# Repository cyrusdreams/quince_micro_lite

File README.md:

# Introduction

The 10-cent-microcontroller, it was everywhere in the news. With a 32bit RISC-V core and useful peripherals, the CH32V003 from WCH is suited to many projects. But such a small microcontroller needs to be programmed via a dedicated adapter. In a forum at mikrocontroller.net, user F.P. analyzed the WCH LinkE debugging adapter and came to the conclusion that the binary code from WCH can be run on the USB enabled CH32V305 microcontroller. And because the CH32V305 can do so much more than its smaller sibling, the idea of this development board was born.

This description is valid for the 'lite' variant of said development board and its second production release version '1.0'.

# Features of the Quince micro lite

-   board dimensions of 21 mm \* 51 mm are the same as a *RaspberryPi Pico*, but it lacks the mounting holes, due to the use of an USB-C connector

-   the pinout of the board is designed to match the peripherals on the *ClockworkPi Pico Calc* mainboard

-   the boards has mounting pads for a microSD card slot and a connector for an OLED screen, if those are mounted, the board has the same features as a *Longan Nano*

-   the *LinkE* debug connector is found on the PCB edge, the "lite" version omits the switchable target supply voltages

-   on the bottom side of the PCB, a CAN bus transceiver can be mounted, this makes the Quince micro a small CAN bus node

-   a RGB LED can be controlled from the microcontroller, two of the LEDs share the port with the Rx/Tx lines of the debug interface

## Pinout of the Quince micro

The coloured signals match the ones on a *Raspberry Pi Pico*.

Remark: ports PB8 and PB9 are exchanged in the v0.9 revision of the *Quince micro lite*.

## Quince micro compared to the Longan nano

On the bottom side of the *Quince micro*, additional parts can be assembled to have a similar functionality as a *Longan nano* development board:

-   microSD slot, the port pins are also available on pins 21, 22, 24 and 25 of the *Quince micro*

-   eight-pin connector for OLED displays

## Quince micro as a CAN bus node

On the bottom side of the PCB, a CAN bus transceiver can be mounted (position U50) with its decoupling capacitor (C51, 100nF) and a four pole SMD pin header. With the available signals CAN-high, CAN-low, 5V-supply and Ground, the Quince micro can be supplied with power and act as a CAN bus node.

Recommended are CAN-SIC transceivers (Signal Improvement Capability), if the additional cost of approximately 0.15€ is bearable for the intended project. These newer transceivers enable higher data rates and/or longer wiring distances than older CAN-FD transceivers. For *Quince micro*, CAN transceivers with 'standby' input and separate IO voltage are suitable. Examples of compatible transceivers are TJA1462 , TCAN1462, TLE9371VSJ and others.

# Quince micro is a Debugger

## Features of the Quince micro as a WCH LinkE Debugger

On the short side of the PCB, opposite of the USB-S connector, there are solder pads suitable for two sets of five pin headers. The pinout is close to the *WCH LinkE R0 1v3*; the power supply pins are not switchable. Also not available is the "ModeSelect" button. Its functionality can be controlled via software, as stated in the "WCH-LinkUserManual" (version V2.4).

## Setup of the Quince micro as a LinkE Debugger

In the forum of mikrocontroller.net, user [Benutzer F.P. (fail)](https://www.mikrocontroller.net/user/show/fail) posted the following [Instructions](https://www.mikrocontroller.net/topic/578672#7974902) that are similar for the *Quince micro*:

1.  Install the software from WCH, commands for Linux:

    1.  git clone https://github.com/ch32-rs/wchisp

    2.  git clone https://github.com/ch32-rs/wlink

2.  Build the software (see respective documentation)

3.  Put the microcontroller into the USB programming mode

    1.  unpower the Quince micro

    2.  push and hold BOOT0 switch

    3.  connect USB to a PC

    4.  release BOOT0 switch

4.  Flash the firmware from MounRiverStudio (see [mikrocontroller.net)](https://www.mikrocontroller.net/attachment/672558/WCH-LinkE-APP-IAP.bin)

    1.  wchisp flash WCH-LinkE-APP-IAP.bin

5.  restart the Quince micro: unplug USB, reconnect USB

Now the Quince micro is ready to function as a WCH-LinkE adapter. After connecting it to another CH32 target (for example another Quince micro), the second microcontroller can be programmed with, for example:

1.  wlink flash blink.bin

The connection to a second Quince micro is done by connecting the pins SWDIO and SWCLK of both boards.

# Developing Software for the Quince micro

## MounRiver Studio

MounRiver Studio is the IDE preferred by WCH.

## Arduino

WCH has released their own Arduino core. With it, the CH32V305-Microcontroller of the Qince micro can be programmed with the Arduino IDE. The board itself is not available in the IDE, but the peripherals can be addressed as on the development board 'CH32V305RBT6'. The following pins (D\* and A\*) are available:

## PlatformIO

There is a GitHub repositry for [CH32V](https://github.com/Community-PIO-CH32V/platform-ch32v) in the PlatformIO IDE.

## cnlohr / ch32fun

Developer and YouTuber CNLohr (Charles) released his own development environment for CH32V with the name [ch32fun](https://github.com/cnlohr/ch32fun) on GitHub.

## Python

There is an [experimental port](https://github.com/r4d10n/micropython-wch-ch32v307/tree/master/ports/wch) of MicroPython for the CH32V307, this should also be useable for the CH32V305.

# Annex

## Revision History

### Revision v0.9

First production data.

### Revision v1.0

-   Changed the connection of PB8 and PB9 to match the RaspberryPi pinout, enabling an additional IC bus.

-   Connected 5V and 3.3V to the debug connector (non-switchable supply)

## Copyright

This text is licensed by CC-BY-SA-4.0. Product names and other trademarks are in the possession of their respective owners. This text makes no claim regarding those names but needs to use them for documentation and clarification purposes.

The Quince micro lite board itself is licensed via CERN-OHL-S-2.0, modifications and improvements are welcome.

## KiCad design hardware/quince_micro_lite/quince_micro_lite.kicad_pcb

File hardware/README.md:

# quince_micro_lite
A CH32V305 development board with Debugger option. Capable of interfacing with a PicoCalc mainboard.

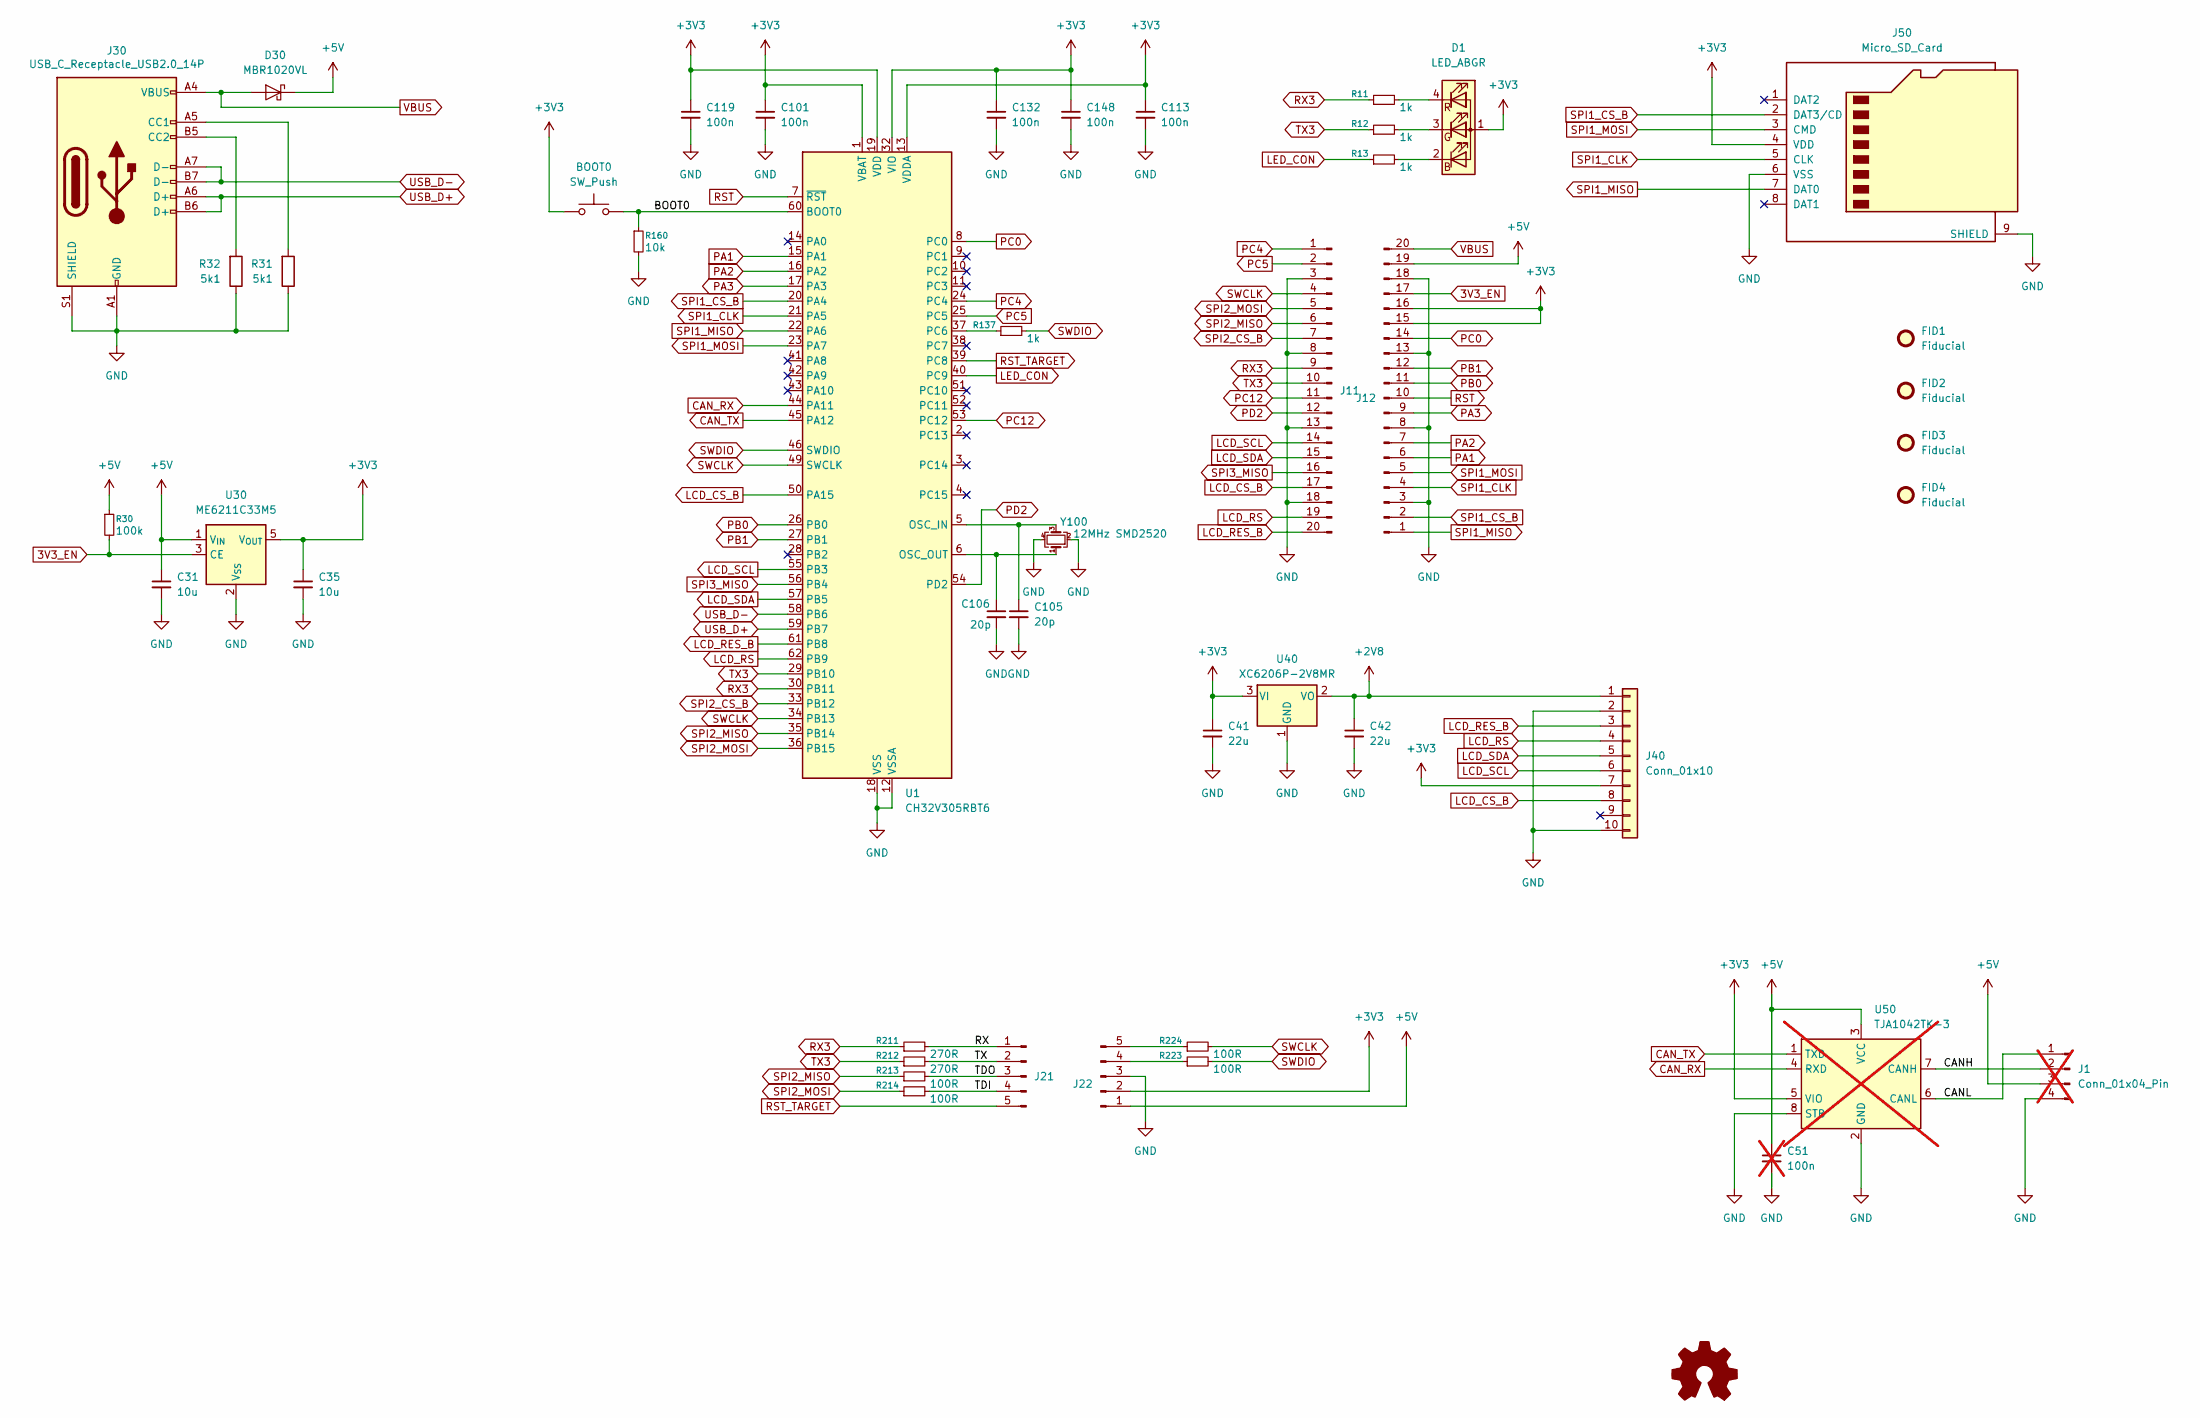
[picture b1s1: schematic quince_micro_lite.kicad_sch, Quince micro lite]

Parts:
BOOT0: SW_Push; SW_SPST_B3U-1000P
C31, C35: 10u; C_0603_1608Metric
C41, C42: 22u; C_0603_1608Metric
C51: 100n; C_0603_1608Metric_Pad1.08x0.95mm_HandSolder; not fitted
C101, C113, C119, C132, C148: 100n; C_0402_1005Metric
C105, C106: 20p; C_0402_1005Metric
D1: LED_ABGR; LED_Cree-PLCC4_2x2mm_CW
D30: MBR1020VL; D_SOD-123F
FID1, FID2, FID3, FID4: Fiducial; Fiducial_0.5mm_Mask1mm
J1: Conn_01x04_Pin; PinHeader_2x02_P2.54mm_Vertical_SMD; not fitted
J11, J12: Conn_01x20_Pin; PinHeader_1x20_P2.54mm_Vertical
J21, J22: Conn_01x05_Pin; Harwin_M20-89005xx_1x05_P2.54mm_Horizontal
J30: USB_C_Receptacle_USB2.0_14P; USB_C_Receptacle_G-Switch_GT-USB-7010ASV
J40: Conn_01x10; Amphenol_F32Q-1A7x1-11008_1x08-1MP_P0.5mm_Horizontal
J50: Micro_SD_Card; microSD_HC_Hirose_DM3D-SF
R11, R12, R13, R137: 1k; R_0402_1005Metric
R30: 100k; R_0402_1005Metric
R31, R32: 5k1; R_0402_1005Metric
R160: 10k; R_0402_1005Metric
R211, R212: 270R; R_0402_1005Metric
R213, R214, R223, R224: 100R; R_0402_1005Metric
U1: CH32V305RBT6; LQFP-64_10x10mm_P0.5mm
U30: ME6211C33M5; SOT-23-5
U40: XC6206P-2V8MR; SOT-23-3
U50: TJA1042TK-3; SO-8_3.9x4.9mm_P1.27mm; not fitted
Y100: 12MHz SMD2520; Crystal_SMD_2520-4Pin_2.5x2.0mm

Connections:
3V3_EN: J12.17, R30.2, U30.3 (CE)
+2V8: C42.1, J40.1, U40.2 (VO)
+3V3: BOOT0.1, C35.1, C41.1, C101.1, C113.1, C119.1, C132.1, C148.1, D1.1 (A), J12.15, J12.16, J22.2, J40.7, J50.4 (VDD), U1.1 (VBAT), U1.13 (VDDA), U1.19 (VDD), U1.32 (VIO), U1.48 (VDD), U1.64 (VIO), U30.5 (V_{OUT}), U40.3 (VI), U50.5 (VIO)
+5V: C31.1, C51.1, D30.1 (K), J1.3, J12.19, J22.1, R30.1, U30.1 (V_{IN}), U50.3 (VCC)
/BOOT0: BOOT0.2, R160.1, U1.60 (BOOT0)
/CANH: J1.2, U50.7 (CANH)
/CANL: J1.1, U50.6 (CANL)
/RX: J21.1, R211.2
/TDI: J21.4, R214.2
/TDO: J21.3, R213.2
/TX: J21.2, R212.2
CAN_RX: U1.44 (PA11), U50.4 (RXD)
CAN_TX: U1.45 (PA12), U50.1 (TXD)
GND: C31.2, C35.2, C41.2, C42.2, C51.2, C101.2, C105.2, C106.2, C113.2, C119.2, C132.2, C148.2, J1.4, J11.3, J11.8, J11.13, J11.18, J12.3, J12.8, J12.13, J12.18, J22.3, J30.A1 (GND), J30.A12 (GND), J30.B1 (GND), J30.B12 (GND), J30.S1 (SHIELD), J40.2, J40.10, J50.6 (VSS), J50.9 (SHIELD), R31.1, R32.1, R160.2, U1.12 (VSSA), U1.18 (VSS), U1.31 (VSS), U1.47 (VSS), U1.63 (VSS), U30.2 (V_{SS}), U40.1 (GND), U50.2 (GND), U50.8 (STB), U50.9 (GND), Y100.2, Y100.4
LCD_CS_B: J11.17, J40.8, U1.50 (PA15)
LCD_RES_B: J11.20, J40.3, U1.61 (PB8)
LCD_RS: J11.19, J40.4, U1.62 (PB9)
LCD_SCL: J11.14, J40.6, U1.55 (PB3)
LCD_SDA: J11.15, J40.5, U1.57 (PB5)
LED_CON: R13.1, U1.40 (PC9)
unnamed: D1.2 (BK), R13.2
unnamed: D1.3 (GK), R12.2
unnamed: D1.4 (RK), R11.2
unnamed: J22.4, R223.1
unnamed: J22.5, R224.1
unnamed: J30.A5 (CC1), R31.2
unnamed: J30.B5 (CC2), R32.2
unnamed: C105.1, U1.5 (OSC_IN), Y100.3
unnamed: C106.1, U1.6 (OSC_OUT), Y100.1
unnamed: R137.1, U1.37 (PC6)
PA1: J12.6, U1.15 (PA1)
PA2: J12.7, U1.16 (PA2)
PA3: J12.9, U1.17 (PA3)
PB0: J12.11, U1.26 (PB0)
PB1: J12.12, U1.27 (PB1)
PC0: J12.14, U1.8 (PC0)
PC4: J11.1, U1.24 (PC4)
PC5: J11.2, U1.25 (PC5)
PC12: J11.11, U1.53 (PC12)
PD2: J11.12, U1.54 (PD2)
RST: J12.10, U1.7 (~RST)
RST_TARGET: J21.5, U1.39 (PC8)
RX3: J11.9, R11.1, R211.1, U1.30 (PB11)
SPI1_CLK: J12.4, J50.5 (CLK), U1.21 (PA5)
SPI1_CS_B: J12.2, J50.2 (DAT3/CD), U1.20 (PA4)
SPI1_MISO: J12.1, J50.7 (DAT0), U1.22 (PA6)
SPI1_MOSI: J12.5, J50.3 (CMD), U1.23 (PA7)
SPI2_CS_B: J11.7, U1.33 (PB12)
SPI2_MISO: J11.6, R213.1, U1.35 (PB14)
SPI2_MOSI: J11.5, R214.1, U1.36 (PB15)
SPI3_MISO: J11.16, U1.56 (PB4)
SWCLK: J11.4, R224.2, U1.34 (PB13), U1.49 (SWCLK)
SWDIO: R137.2, R223.2, U1.46 (SWDIO)
TX3: J11.10, R12.1, R212.1, U1.29 (PB10)
USB_D+: J30.A6 (D+), J30.B6 (D+), U1.59 (PB7)
USB_D-: J30.A7 (D-), J30.B7 (D-), U1.58 (PB6)
VBUS: D30.2 (A), J12.20, J30.A4 (VBUS), J30.A9 (VBUS), J30.B4 (VBUS), J30.B9 (VBUS)

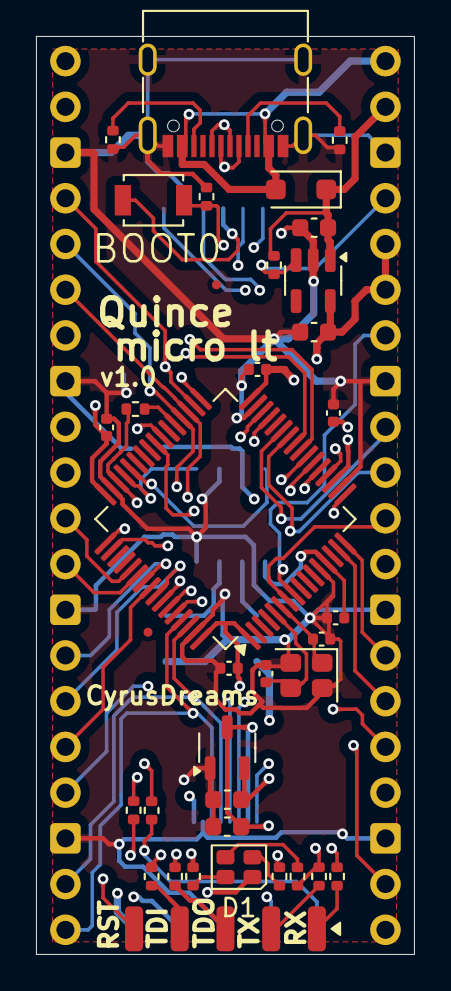
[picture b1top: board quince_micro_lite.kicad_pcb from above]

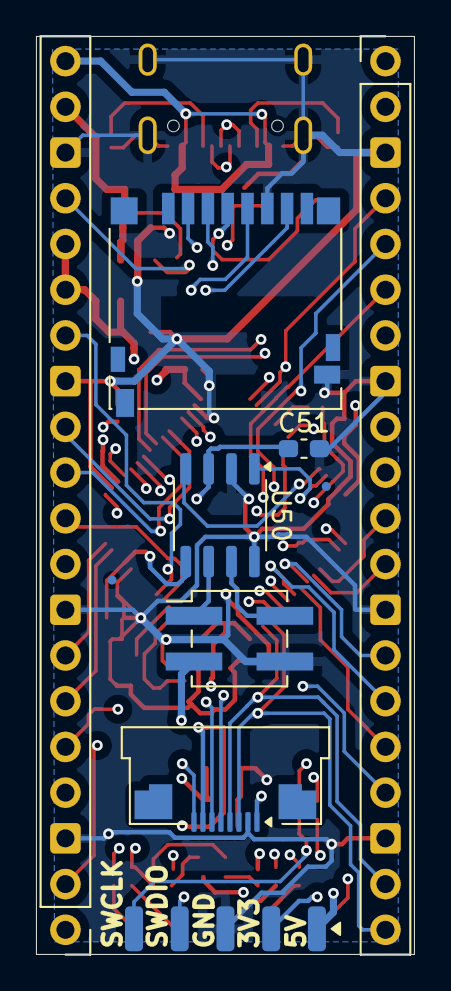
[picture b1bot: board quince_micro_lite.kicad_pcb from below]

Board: 4 copper layers, 21.0 x 51.0 mm, 46 parts (10 on the bottom side), 57 nets.

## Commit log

2025-12-30 Create LICENSE.md
    CERN Open Hardware Licence Version 2 - Strongly Reciprocal
2025-12-30 Update LICENSE.md
    make it MD format compatible
2025-12-30 first production data
2025-12-30 documentation initial commit
2026-01-27 version 1.0 commit, changed PB8 and PB9, added 5V and 3.3V supply to debug connector
